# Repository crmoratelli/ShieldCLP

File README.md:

# ShieldCLP

  The following project refers to one of the steps in the development of an Open Source PLC with a web interface using Raspberry Pi.
The hardware was developed with the aim of integrating 8 of the microcontroller GPIO's as digital inputs-outputs for the PLC platform, leaving the other ports at the user's disposal.

The shield will allow connection to an N4DBA06 module to support analog inputs and outputs.

The RPI and the N4DBA06 module will be powered through the shield.

The power supply used must have a voltage output of 12Vdc.

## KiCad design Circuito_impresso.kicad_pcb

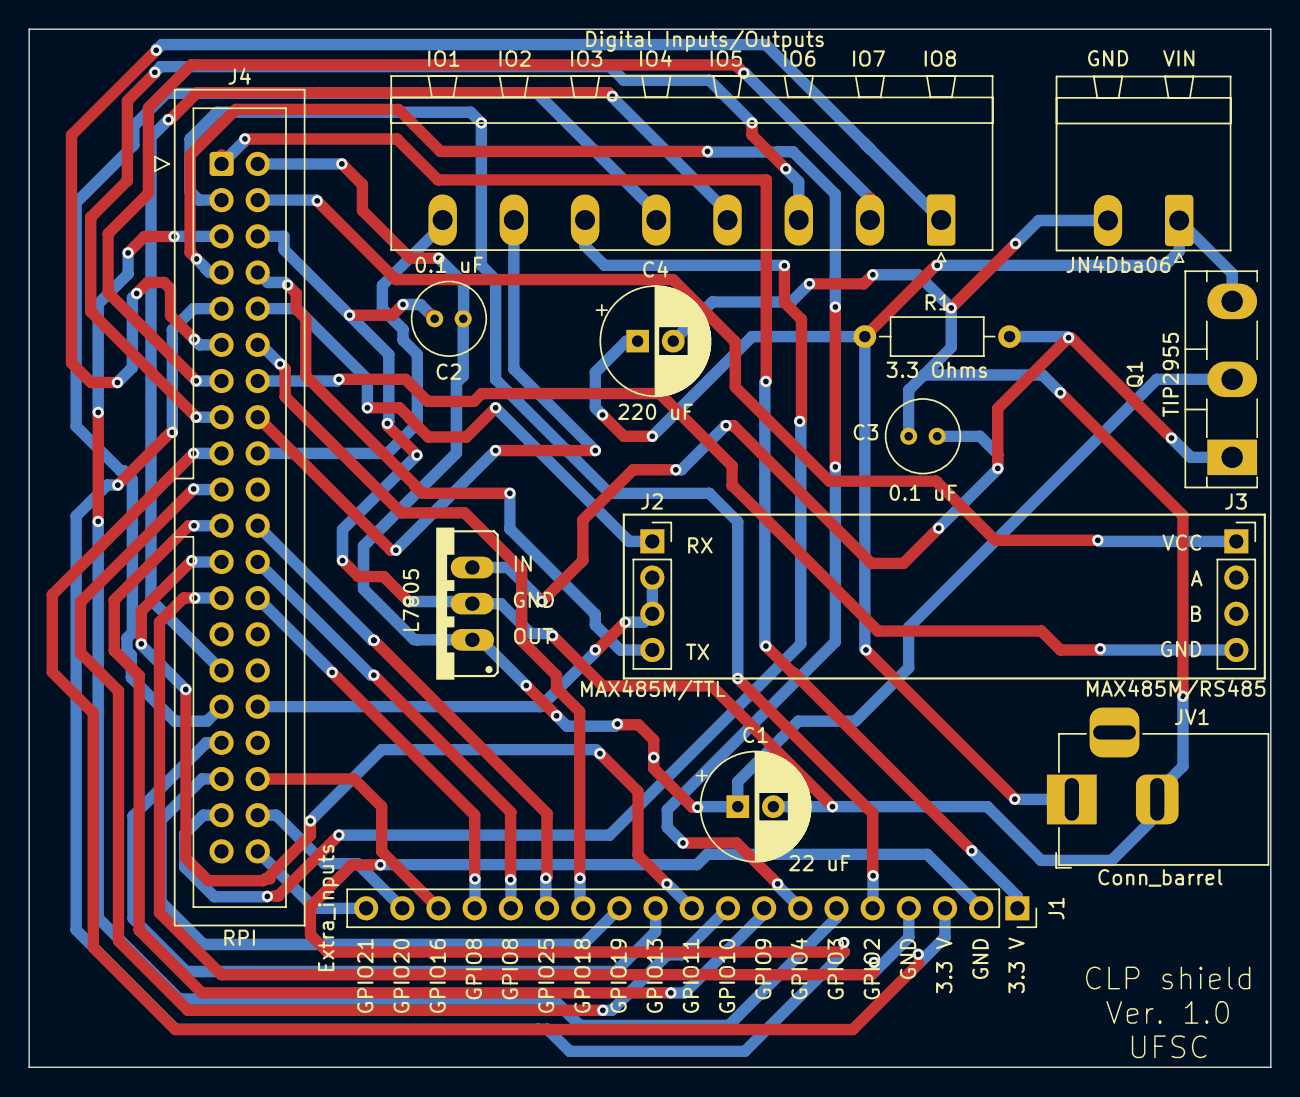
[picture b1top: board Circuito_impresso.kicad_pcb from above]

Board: 2 copper layers, 87.2 x 72.9 mm, 14 parts (0 on the bottom side), 36 nets.

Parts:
C1: 22 uF; CP_Radial_D7.5mm_P2.50mm
C2, C3: 0.1 uF; C_Radial_D5.0mm_H5.0mm_P2.00mm
C4: 220 uF; CP_Radial_D7.5mm_P2.50mm
J1: Extra_inputs; PinSocket_1x19_P2.54mm_Vertical
J2: MAX485M/TTL; PinSocket_1x04_P2.54mm_Vertical
J3: MAX485M/RS485; PinSocket_1x04_P2.54mm_Vertical
J4: RPI; IDC-Header_2x20_P2.54mm_Vertical
JIO-1: Digital Inputs/Outputs; PhoenixContact_MSTBA_2,5_8-G_1x08_P5.00mm_Horizontal
JN4Dba06: Conn_01x02; PhoenixContact_MSTBA_2,5_2-G_1x02_P5.00mm_Horizontal
JV1: Conn_barrel; BarrelJack_Horizontal
Q1: TIP2955; TO-218-3_Vertical
R1: 3.3 Ohms; R_Axial_DIN0207_L6.3mm_D2.5mm_P10.16mm_Horizontal
U1: L7805; 78XXS

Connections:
unnamed: C1.1, C2.1, J4.2, Q1.2 (C), U1.3 (IN)
unnamed: C1.2, C2.2, C3.2, C4.2, J4.6, JN4Dba06.2, JV1.2, U1.2 (GND)
unnamed: C3.1, Q1.1 (B), R1.2, U1.1 (OUT)
unnamed: C4.1, JN4Dba06.1, JV1.1, Q1.3 (E), R1.1
unnamed: J1.1, J4.1
unnamed: J1.2, J4.9
unnamed: J1.3, J4.17
unnamed: J1.4, J4.25
unnamed: J1.5, J4.3
unnamed: J1.6, J4.5
unnamed: J1.7, J4.7
unnamed: J1.8, J4.21
unnamed: J1.9, J4.19
unnamed: J1.10, J4.23
unnamed: J1.11, J4.33
unnamed: J1.12, J4.35
unnamed: J1.13, J4.12
unnamed: J1.14, J4.22
unnamed: J1.15, J4.24
unnamed: J1.16, J4.26
unnamed: J1.17, J4.36
unnamed: J1.18, J4.38
unnamed: J1.19, J4.40
unnamed: J2.1, J4.10
unnamed: J2.2, J2.3, J4.32
unnamed: J2.4, J4.8
unnamed: J3.1, J4.4
unnamed: J3.4, J4.14
unnamed: J4.11, JIO-1.1
unnamed: J4.13, JIO-1.2
unnamed: J4.15, JIO-1.3
unnamed: J4.16, JIO-1.7
unnamed: J4.18, JIO-1.8
unnamed: J4.29, JIO-1.4
unnamed: J4.31, JIO-1.5
unnamed: J4.37, JIO-1.6

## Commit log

2022-10-03 Initial Commit
    The schematic is structured and ready. the footprints have been assigned. And the preliminary position of the components on the PCB has been established.
    However, there is a footprint reference to one of the components by a path in the local machine that may not work at first (to be corrected). One of the components on the PCB did not have its connect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
2022-10-03 Creates README file
2022-10-04 Finalizes the preliminary design of the PCB
2022-10-06 updates to meet requirements; error correction
    the width of the tracks is now 0.8 mm (considering the maximum circuit current of 5 amps, with a maximum increase of 40°C; the position of each terminal of the l7805 in the schematic has been correct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
    The silkscreen must be done
2022-10-10 Error correction; silkscreen insertion.
    The L7805 terminals were inverted on the PCB and have been fixed in this version;
    The identification of some of the terminals was made by inserting the serigraphy of the board
2022-10-19 Adjustments
    Capacitors C2 and C3 have been upgraded from SMD to not polarized through hole; the radius of C1 has been updated; inserted pcb version.
2022-12-06 Gerber and drill files submission
